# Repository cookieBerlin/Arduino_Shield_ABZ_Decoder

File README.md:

# Arduino_Shield_ABZ_Decoder

This board uses the IC-Haus IC-MD IC to count ABZ pulses.

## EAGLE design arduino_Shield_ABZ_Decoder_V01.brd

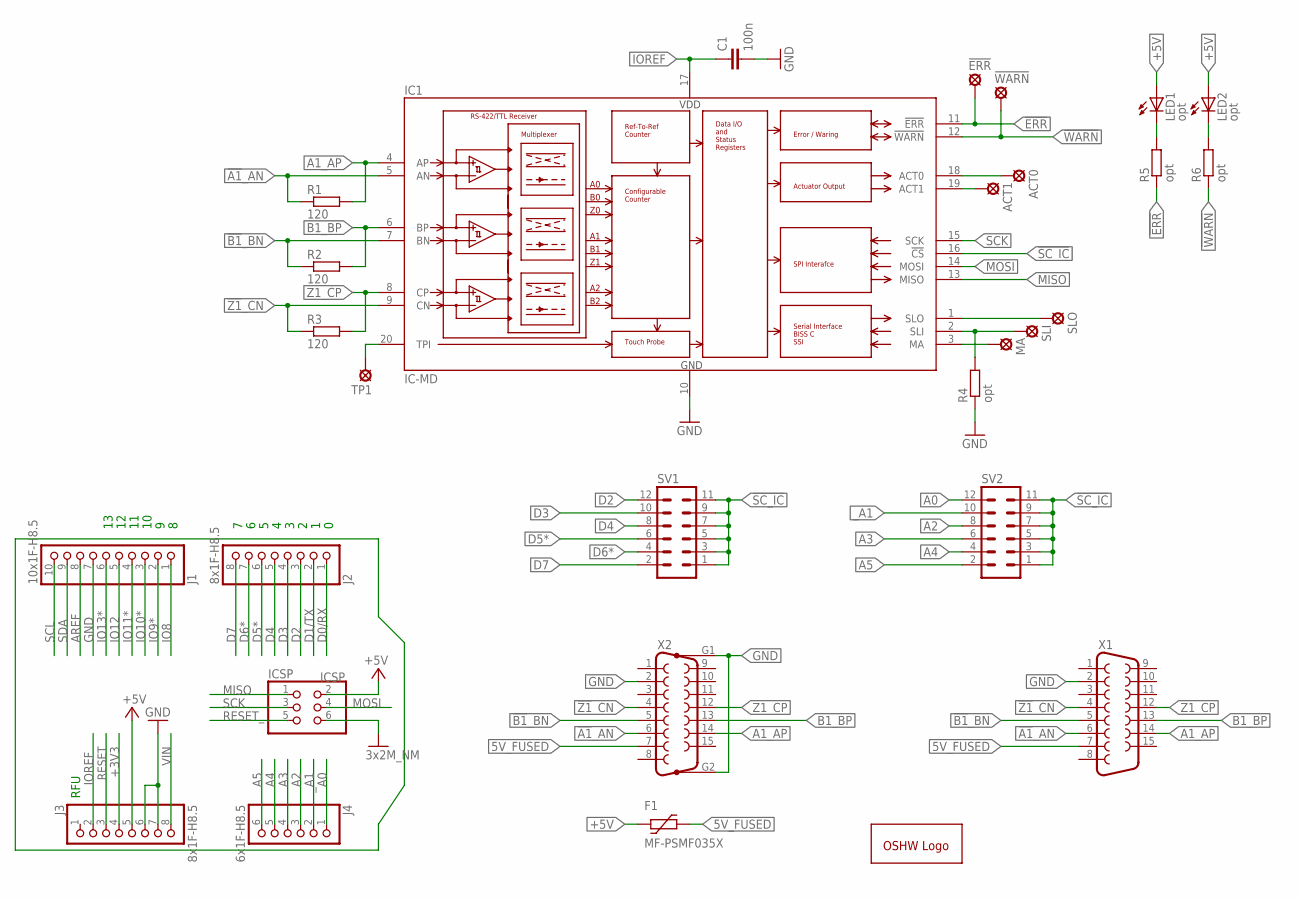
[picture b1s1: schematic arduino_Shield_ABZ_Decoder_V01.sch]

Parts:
!ERR: LSP10
!WARN: LSP10
ACT0, ACT1: LSP10
C1: 100n; C0805
F1: MF-PSMF035X; F0805
GOLD_ORB_SM1: OSHWLOGOLOGO8MM; OSHW_8MM
IC1: IC-MD; TSSOP20
ICSP: ICSP; 2X03
J1: 10x1F-H8.5; 1X10
J2, J3: 8x1F-H8.5; 1X08
J4: 6x1F-H8.5; 1X06
LED1, LED2: opt; LED3MM
MA: LSP10
R1, R2, R3: 120; M1206
R4, R5, R6: opt; M1206
SLI: LSP10
SLO: LSP10
SV1, SV2: MA06-2
TP1: LSP10
X1: F15D
X2: F15HP

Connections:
5V_FUSED: F1.2, X1.7, X2.7
!A1!_AN: IC1.5 (AN), R1.1, X1.6, X2.6
!B1!_BN: IC1.7 (BN), R2.1, X1.5, X2.5
!ERR: !ERR.MP, IC1.11 (!ERR), R5.1
!SC_IC: IC1.16 (!CS), SV1.1, SV1.3, SV1.5, SV1.7, SV1.9, SV1.11, SV2.1, SV2.3, SV2.5, SV2.7, SV2.9, SV2.11
!WARN: !WARN.MP, IC1.12 (!WARN), R6.1
!Z1!_CN: IC1.9 (CN), R3.1, X1.4, X2.4
+3V3: J3.4
+5V: F1.1, ICSP.2, J3.5, LED1.A, LED2.A
A0: J4.1, SV2.12
A1_AP: IC1.4 (AP), R1.2, X1.14, X2.14
A2: J4.3, SV2.8
A3: J4.4, SV2.6
A4: J4.5, SV2.4
A5: J4.6, SV2.2
ACT0: ACT0.MP, IC1.18 (ACT0)
ACT1: ACT1.MP, IC1.19 (ACT1)
AREF: J1.8
B1_BP: IC1.6 (BP), R2.2, X1.13, X2.13
D0/RX: J2.1
D1/TX: J2.2
D2: J2.3, SV1.12
D3: J2.4, SV1.10
D4: J2.5, SV1.8
D5*: J2.6, SV1.6
D6*: J2.7, SV1.4
D7: J2.8, SV1.2
GND: C1.2, IC1.10 (GND), ICSP.6, J1.7, J3.6, J3.7, R4.1, X1.2, X2.2, X2.G1, X2.G2
IO8: J1.1
IO9*: J1.2
IO10*: J1.3
IO11*: J1.4
IO12: J1.5
IO13*: J1.6
IOREF: C1.1, IC1.17 (VDD), J3.2
MA: IC1.3 (MA), MA.MP
MISO: IC1.13 (MISO), ICSP.1
MOSI: IC1.14 (MOSI), ICSP.4
unnamed: LED1.K (C), R5.2
unnamed: LED2.K (C), R6.2
RESET: J3.3
RESET_: ICSP.5
SCK: IC1.15 (SCK), ICSP.3
SCL: J1.10
SDA: J1.9
SLI: IC1.2 (SLI), R4.2, SLI.MP
SLO: IC1.1 (SLO), SLO.MP
TP1: IC1.20 (TPI), TP1.MP
VIN: J3.8
Z1_CP: IC1.8 (CP), R3.2, X1.12, X2.12
_A1: J4.2, SV2.10

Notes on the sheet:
RFU

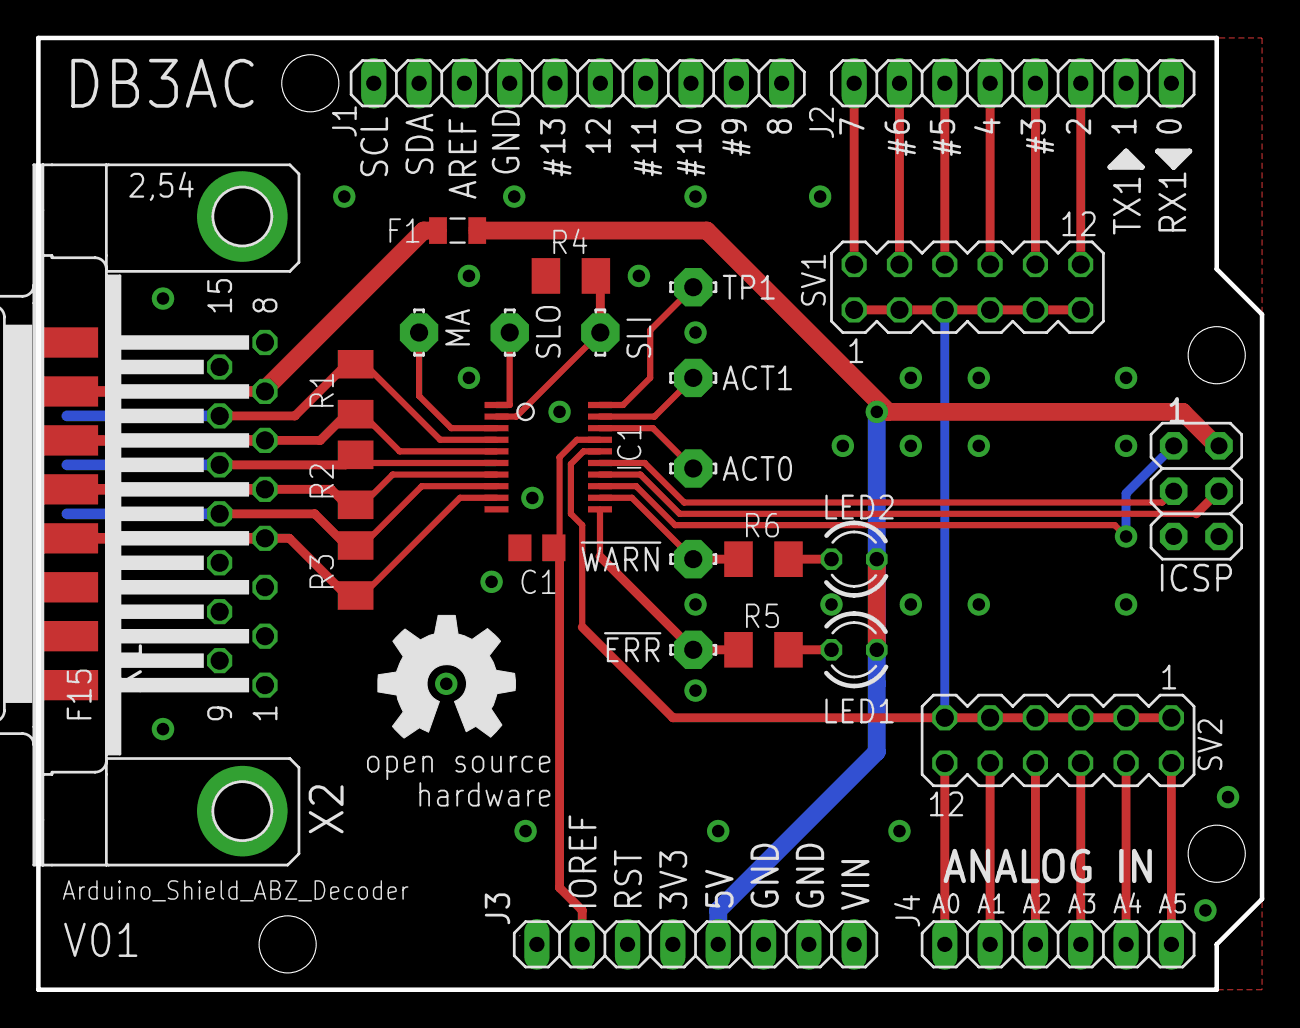
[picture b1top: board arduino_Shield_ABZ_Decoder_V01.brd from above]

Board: 2 copper layers, 68.6 x 53.3 mm, 29 parts (0 on the bottom side), 36 nets.

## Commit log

2019-06-20 add V01
